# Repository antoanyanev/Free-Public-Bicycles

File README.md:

# Free-Public-Bicycles
Free Public Bicycles Diploma Project

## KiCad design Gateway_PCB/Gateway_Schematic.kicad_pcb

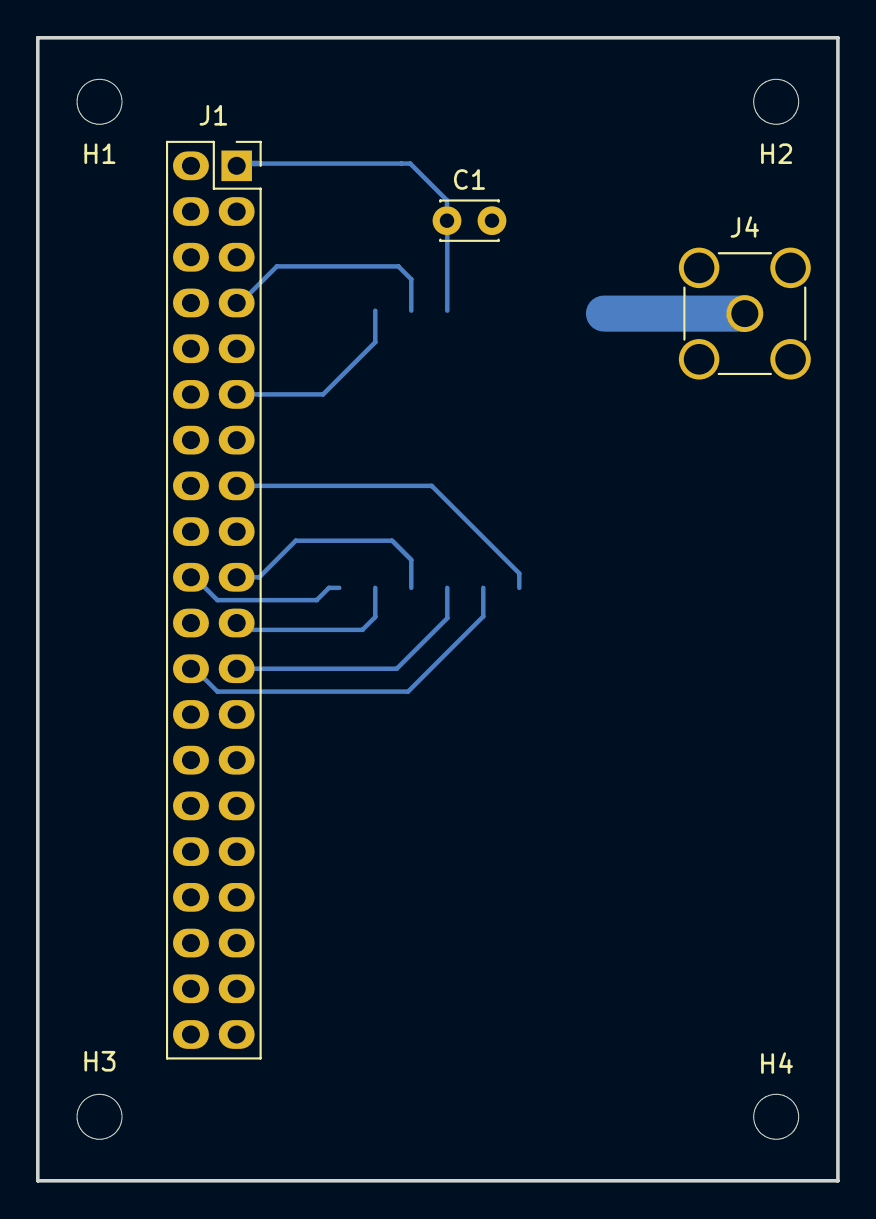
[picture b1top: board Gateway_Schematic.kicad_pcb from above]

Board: 2 copper layers, 44.4 x 63.5 mm, 8 parts (0 on the bottom side), 8 nets.

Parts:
C1: 100n; C_Disc_D3.0mm_W2.0mm_P2.50mm
H1, H2, H3, H4: MountingHole_2.5mm
J1: Conn_01x40_Female; PinSocket_2x20_P2.54mm_Vertical
J4: Conn_01x01_Female; SMA_Amphenol_901-144_Vertical
U1: RFM95W-868S2; XCVR_RFM95W-915S2

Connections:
DIO0: J1.7, U1.14
DIO1: J1.11, U1.15
GND: J1.20, J1.39, U1.1, U1.8, U1.10
MISO: J1.21, U1.2
MOSI: J1.19, U1.3
NSS: J1.24, U1.5
RST: J1.15, U1.6
SCK: J1.23, U1.4

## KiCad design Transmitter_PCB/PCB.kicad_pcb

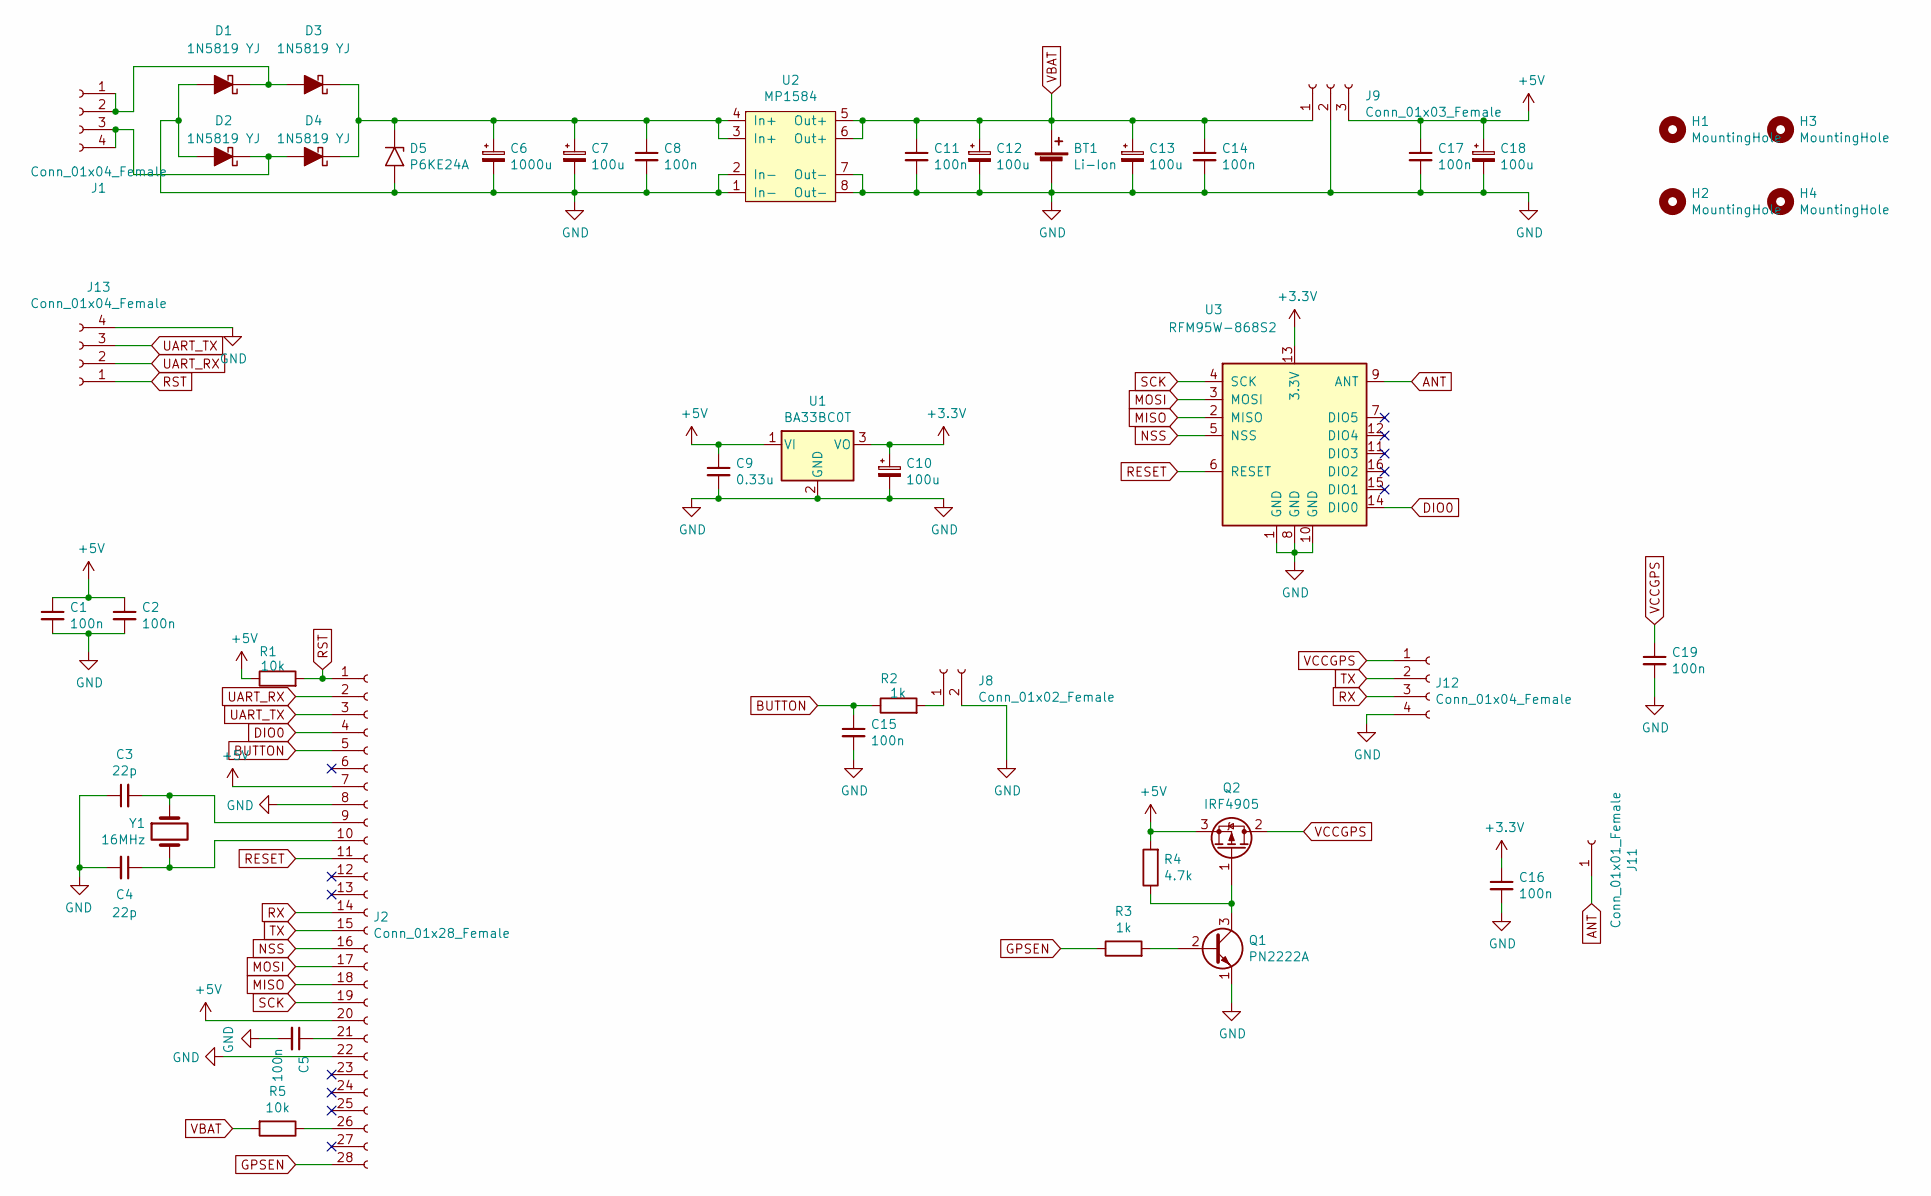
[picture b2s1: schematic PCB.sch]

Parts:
BT1: Li-Ion; Battery_Holder
C1, C2, C5, C8, C11, C14, C15, C16, C17, C19: 100n; C_Disc_D3.0mm_W2.0mm_P2.50mm
C3, C4: 22p; C_Disc_D5.0mm_W2.5mm_P2.50mm
C6: 1000u; CP_Radial_D10.0mm_P5.00mm
C7, C10, C12, C13, C18: 100u; CP_Radial_D5.0mm_P2.00mm
C9: 0.33u; C_Disc_D5.0mm_W2.5mm_P5.00mm
D1, D2, D3, D4: 1N5819 YJ; D_DO-41_SOD81_P10.16mm_Horizontal
D5: P6KE24A; D_DO-15_P15.24mm_Horizontal
H1, H2, H3, H4: MountingHole; MountingHole_3.5mm_Pad_Via
J1: Conn_01x04_Female; Molex_KK-396_A-41791-0004_1x04_P3.96mm_Vertical
J2: Conn_01x28_Female; DIP-28_W7.62mm
J8: Conn_01x02_Female; Molex_KK-254_AE-6410-02A_1x02_P2.54mm_Vertical
J9: Conn_01x03_Female; PinSocket_1x03_P2.54mm_Vertical
J11: Conn_01x01_Female; SMA_Amphenol_901-144_Vertical
J12, J13: Conn_01x04_Female; PinSocket_1x04_P2.54mm_Vertical
Q1: PN2222A; TO-92_Inline
Q2: IRF4905; TO-220-3_Vertical
R1, R5: 10k; R_Axial_DIN0207_L6.3mm_D2.5mm_P10.16mm_Horizontal
R2, R3: 1k; R_Axial_DIN0207_L6.3mm_D2.5mm_P10.16mm_Horizontal
R4: 4.7k; R_Axial_DIN0207_L6.3mm_D2.5mm_P10.16mm_Horizontal
U1: BA33BC0T; TO-220-3_Vertical
U2: MP1584
U3: RFM95W-868S2; RFM95W_THT
Y1: 16MHz; Crystal_HC49-U_Vertical

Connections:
+3V3: C10.1, C16.1, U1.3 (VO), U3.13 (3.3V)
+5V: C1.1, C2.1, C9.1, C17.1, C18.1, J2.7, J2.20, J9.3, Q2.3 (S), R1.1, R4.2, U1.1 (VI)
ANT: J11.1, U3.9 (ANT)
BUTTON: C15.1, J2.5, R2.1
DIO0: J2.4, U3.14 (DIO0)
GND: BT1.2 (-), C1.2, C2.2, C3.1, C4.2, C5.2, C6.2, C7.2, C8.2, C9.2, C10.2, C11.2, C12.2, C13.2, C14.2, C15.2, C16.2, C17.2, C18.2, C19.2, D1.2 (A), D2.2 (A), D5.2 (A2), J2.8, J2.22, J8.2, J9.2, J12.4, J13.4, Q1.1 (E), U1.2 (GND), U2.1 (In-), U2.2 (In-), U2.7 (Out-), U2.8 (Out-), U3.1 (GND), U3.8 (GND), U3.10 (GND)
GPSEN: J2.28, R3.1
MISO: J2.18, U3.2 (MISO)
MOSI: J2.17, U3.3 (MOSI)
NSS: J2.16, U3.5 (NSS)
unnamed: C3.2, J2.9, Y1.1
unnamed: C4.1, J2.10, Y1.2
unnamed: C5.1, J2.21
unnamed: C6.1, C7.1, C8.1, D3.1 (K), D4.1 (K), D5.1 (A1), U2.3 (In+), U2.4 (In+)
unnamed: D1.1 (K), D3.2 (A), J1.1, J1.2
unnamed: D2.1 (K), D4.2 (A), J1.3, J1.4
unnamed: J2.26, R5.1
unnamed: J8.1, R2.2
unnamed: Q1.2 (B), R3.2
unnamed: Q1.3 (C), Q2.1 (G), R4.1
RESET: J2.11, U3.6 (RESET)
RST: J2.1, J13.1, R1.2
RX: J2.14, J12.3
SCK: J2.19, U3.4 (SCK)
TX: J2.15, J12.2
UART_RX: J2.2, J13.2
UART_TX: J2.3, J13.3
VBAT: BT1.1 (+), C11.1, C12.1, C13.1, C14.1, J9.1, R5.2, U2.5 (Out+), U2.6 (Out+)
VCCGPS: C19.1, J12.1, Q2.2 (D)

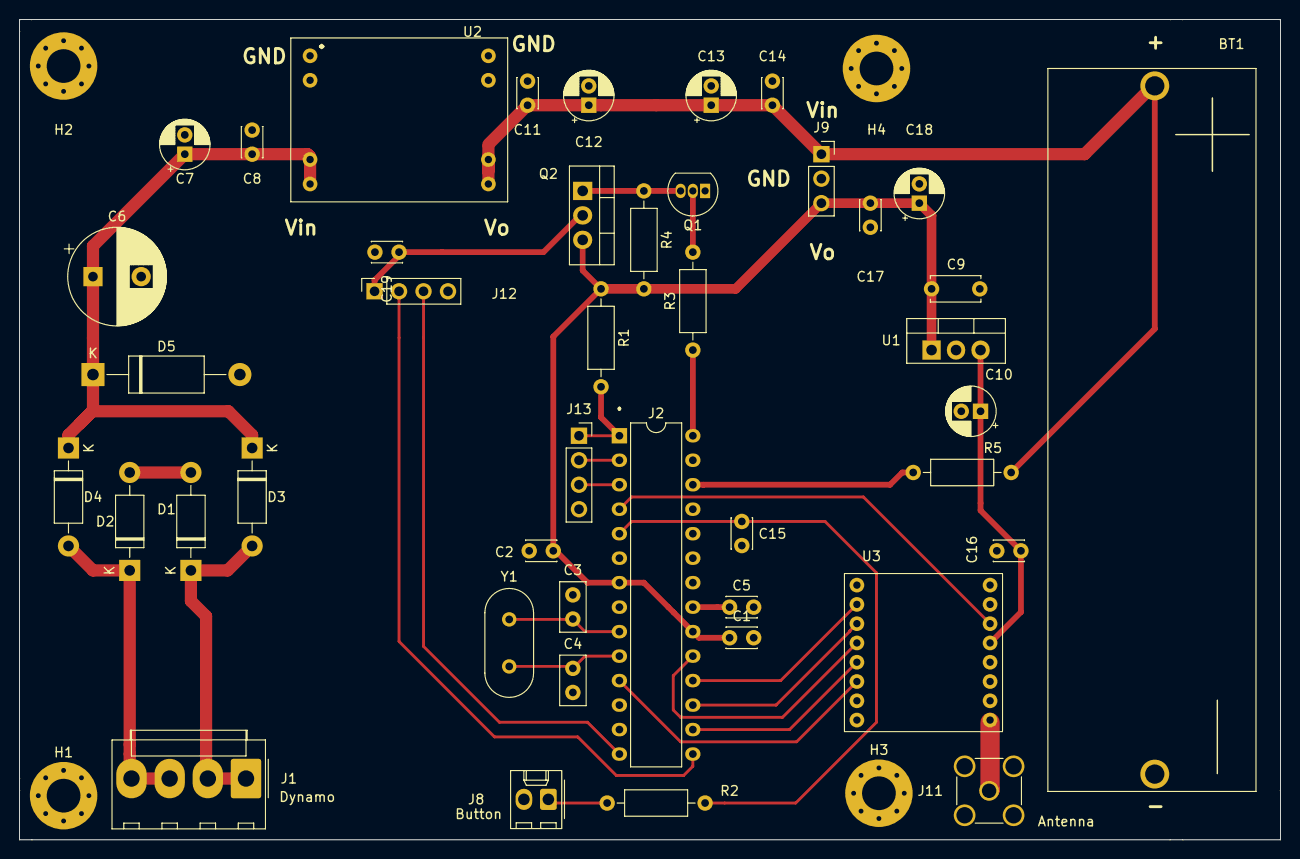
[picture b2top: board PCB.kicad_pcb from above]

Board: 2 copper layers, 130.8 x 85.1 mm, 47 parts (0 on the bottom side), 29 nets.

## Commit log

2019-11-27 Fixed performence issue
2019-12-26 Sending GPS information
2020-01-05 Fixed Transmitter File
2020-01-07 Added Web Application
2020-01-08 Added markers, popups, and renting business logic
2020-01-09 Added battery level icons, address field in pop up, changed port to 442 for https, created a self signed SLL certificate, added auto marker refresh, adder user location marker, added additional butto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
2020-01-10 Fixed marker opening bug, renting and leting go of bicycles
2020-01-12 Fixed let go bug
2020-01-14 Added trips aggregation and sequence number display
2020-01-18 Sync commit
2020-01-18 Fixed transmitter send interval
2020-01-21 Fixed transmitter output format
2020-01-21 Added validation to /locations/add request
2020-01-21 Added gateway file
2020-01-23 Added transmitter schematic
2020-01-26 Added PCB design
2020-01-26 Added Sleep Modes
2020-01-26 Restructurized files
2020-01-26 Removed .vscode folder
2020-01-27 Added PCB images
2020-01-27 Added GPS control logic
2020-01-28 fixed PCB layout and transmitter data fetch bug
2020-01-28 Added button interrupt
2020-01-29 Finished Transmitter code and PCB
2020-01-29 Updated Schematic and PCB
2020-01-29 Added Mounting Holes For Battery holder
2020-01-29 Rotated LoRa Module
2020-01-29 Moved Crystal Capacitors
2020-01-29 Updated PCB Images
2020-01-29 Added UART Header
2020-02-01 Fixed trips bug
2020-02-01 Added batter measuring resistor
2020-02-01 Added battery level measurement and transmission
2020-02-01 Added batter level reading
2020-02-01 Fixed trips numbering bug
2020-02-01 Fixed auto user location centering on startup
2020-02-02 Added Gateway Schematic and PCB files
2020-02-02 Changed RFM95W footprint and added SMA Connector Model
2020-02-03 Added design to the website and registration validation
2020-02-03 Added DIO0 and DIO1
2020-02-04 Added packet validation
2020-02-04 Added login/register input autofocus
2020-02-04 Refactored index.js
2020-02-04 Refactored map.js & profile.js, added map styles file styles.js
2020-02-05 Fixed LoRa socket
2020-02-05 Added automatic letting go of bicycles after 24 hours of inactivivty
2020-02-06 Fixed Transmitter PCB Spacing
2020-02-06 Added Critical Battery Level Shutdown
2020-02-07 Added 3d models
2020-02-07 Added Gerber Files
2020-02-07 Changed SSL certificate
2020-02-16 Added changes to schematics
2020-02-19 Added setup and main methods
2020-02-23 Added power saving mode
2020-02-29 Changed message identification
